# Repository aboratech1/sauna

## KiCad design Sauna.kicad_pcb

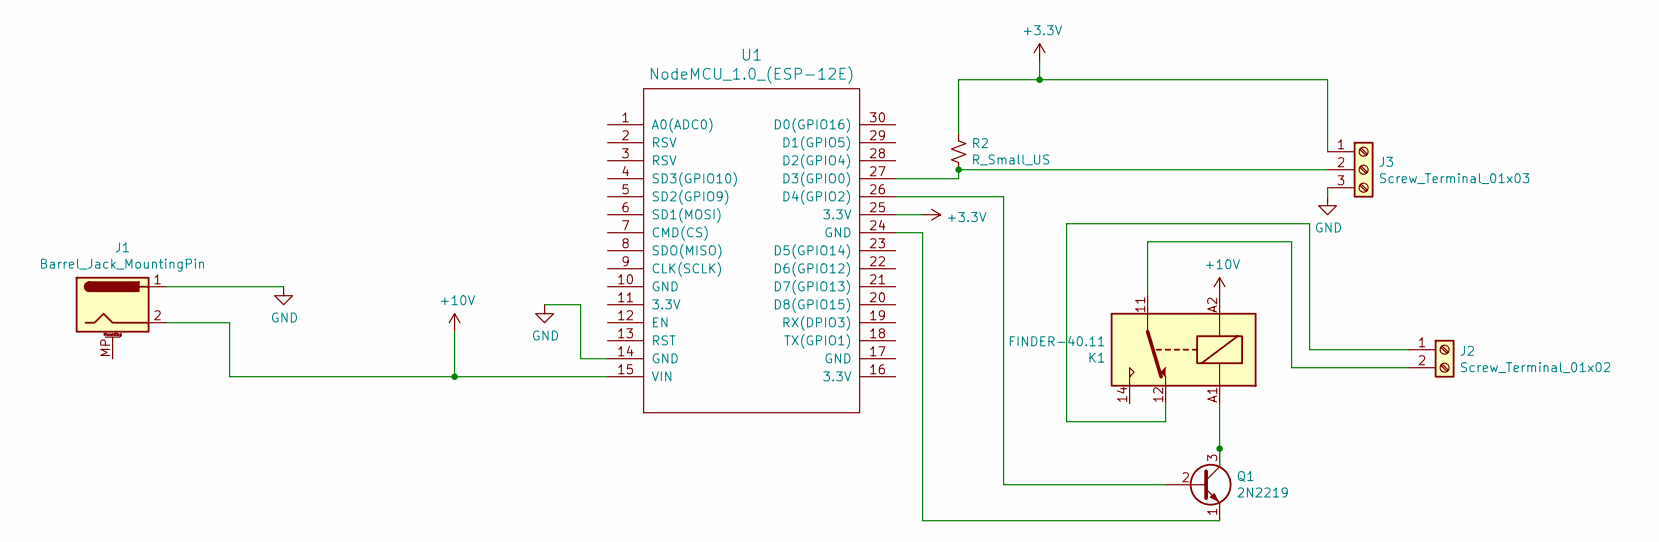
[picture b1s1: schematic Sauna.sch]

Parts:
J1: Barrel_Jack_MountingPin; BarrelJack_Horizontal
J2: Screw_Terminal_01x02; TerminalBlock_4Ucon_1x02_P3.50mm_Horizontal
J3: Screw_Terminal_01x03; TerminalBlock_4Ucon_1x03_P3.50mm_Vertical
K1: FINDER-40.11; Relay_SPDT_Finder_40.11
Q1: 2N2219; TO-39-3
R2: R_Small_US; R_0603_1608Metric_Pad1.05x0.95mm_HandSolder
U1: NodeMCU_1.0_(ESP-12E); NodeMCU1.0(12-E)

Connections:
+3V3: J3.1, R2.1, U1.25 (3.3V)
+10V: J1.2, K1.A2, U1.15 (VIN)
GND: J1.1, J3.3, U1.14 (GND)
unnamed: J2.1, K1.12
unnamed: J2.2, K1.11
unnamed: J3.2, R2.2, U1.27 (D3(GPIO0))
unnamed: K1.A1, Q1.3 (C)
unnamed: Q1.1 (E), U1.24 (GND)
unnamed: Q1.2 (B), U1.26 (D4(GPIO2))

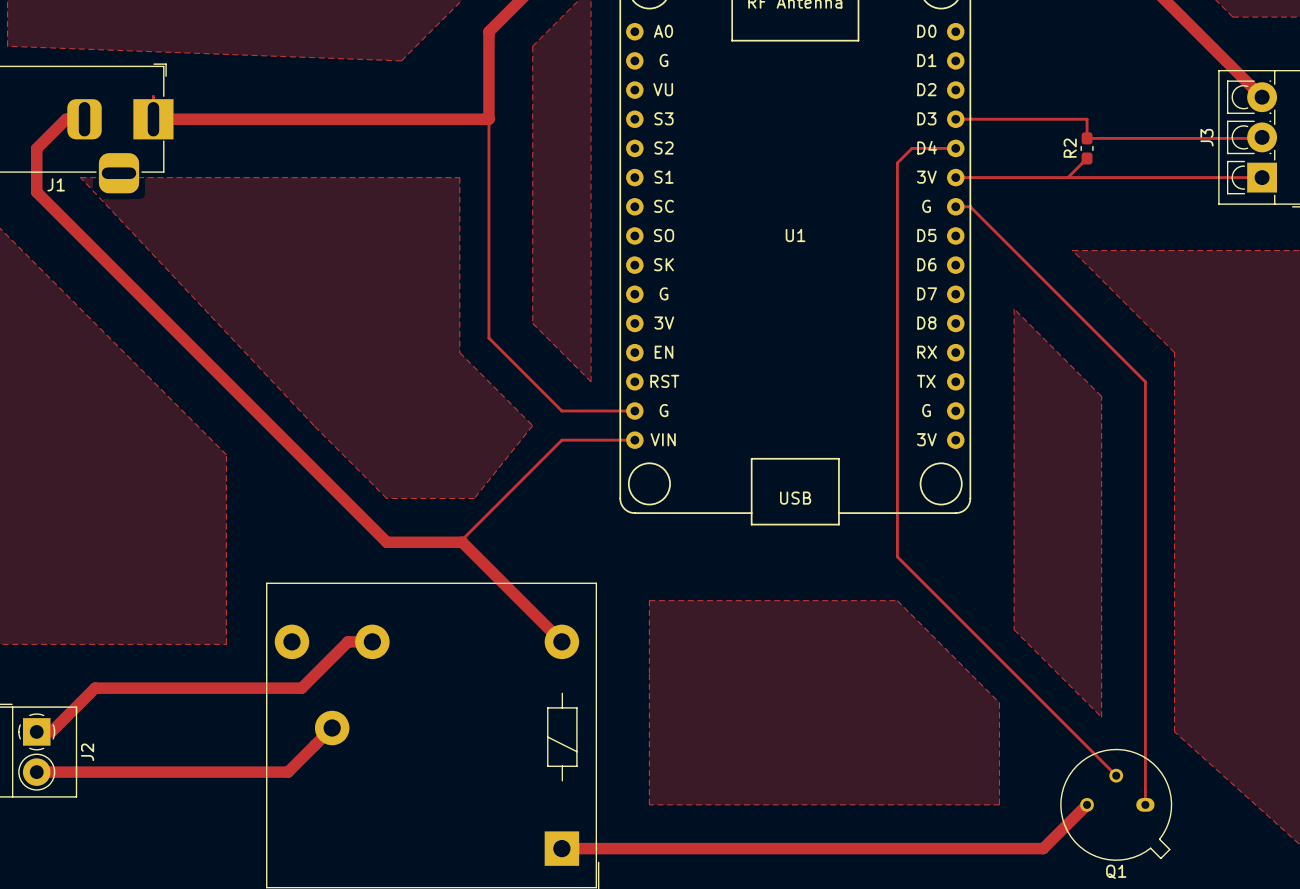
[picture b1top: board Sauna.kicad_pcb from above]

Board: 2 copper layers, 7 parts (0 on the bottom side), 9 nets.

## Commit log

2018-11-14 Initial upload
2018-11-14 ver1
2018-11-14 ver 0 .1
2018-11-14 ver 0.11
